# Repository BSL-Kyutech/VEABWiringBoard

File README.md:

# VEABWiringBoard
A board (60mm x 185mm) for wiring Festo's VEAB valves to VEABControlShield

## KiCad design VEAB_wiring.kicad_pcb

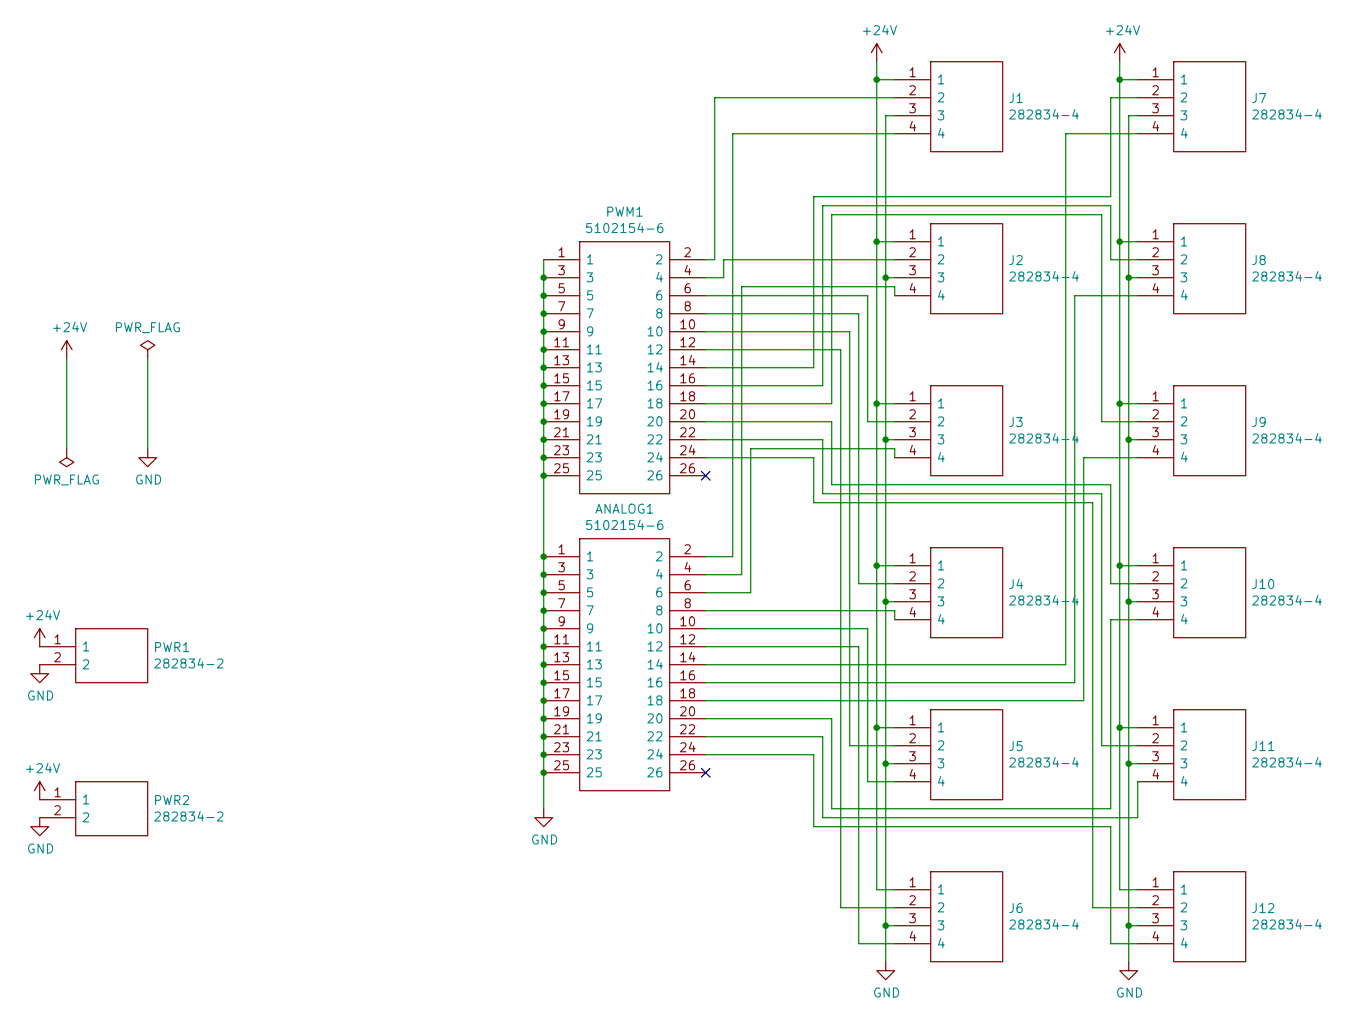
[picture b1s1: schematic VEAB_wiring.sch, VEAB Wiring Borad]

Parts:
ANALOG1: 5102154-6; SHDR26W66P254_2X13_4051X986X927P; Manufacturer_Part_Number 5102154-6
J1, J2, J3, J4, J5, J6, J7, J8, J9, J10, J11, J12: 282834-4; 2828344; Manufacturer_Part_Number 282834-4
PWM1: 5102154-6; SHDR26W66P254_2X13_4051X986X927P; Manufacturer_Part_Number 5102154-6
PWR1, PWR2: 282834-2; 282834-2_1; Manufacturer_Part_Number 282834-2

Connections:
+24V: J1.1, J2.1, J3.1, J4.1, J5.1, J6.1, J7.1, J8.1, J9.1, J10.1, J11.1, J12.1, PWR1.1, PWR2.1
GND: ANALOG1.1, ANALOG1.3, ANALOG1.5, ANALOG1.7, ANALOG1.9, ANALOG1.11, ANALOG1.13, ANALOG1.15, ANALOG1.17, ANALOG1.19, ANALOG1.21, ANALOG1.23, ANALOG1.25, J1.3, J2.3, J3.3, J4.3, J5.3, J6.3, J7.3, J8.3, J9.3, J10.3, J11.3, J12.3, PWM1.1, PWM1.3, PWM1.5, PWM1.7, PWM1.9, PWM1.11, PWM1.13, PWM1.15, PWM1.17, PWM1.19, PWM1.21, PWM1.23, PWM1.25, PWR1.2, PWR2.2
unnamed: ANALOG1.2, J1.4
unnamed: ANALOG1.4, J2.4
unnamed: ANALOG1.6, J3.4
unnamed: ANALOG1.8, J4.4
unnamed: ANALOG1.10, J5.4
unnamed: ANALOG1.12, J6.4
unnamed: ANALOG1.14, J7.4
unnamed: ANALOG1.16, J8.4
unnamed: ANALOG1.18, J9.4
unnamed: ANALOG1.20, J10.4
unnamed: ANALOG1.22, J11.4
unnamed: ANALOG1.24, J12.4
unnamed: J1.2, PWM1.2
unnamed: J2.2, PWM1.4
unnamed: J3.2, PWM1.6
unnamed: J4.2, PWM1.8
unnamed: J5.2, PWM1.10
unnamed: J6.2, PWM1.12
unnamed: J7.2, PWM1.14
unnamed: J8.2, PWM1.16
unnamed: J9.2, PWM1.18
unnamed: J10.2, PWM1.20
unnamed: J11.2, PWM1.22
unnamed: J12.2, PWM1.24

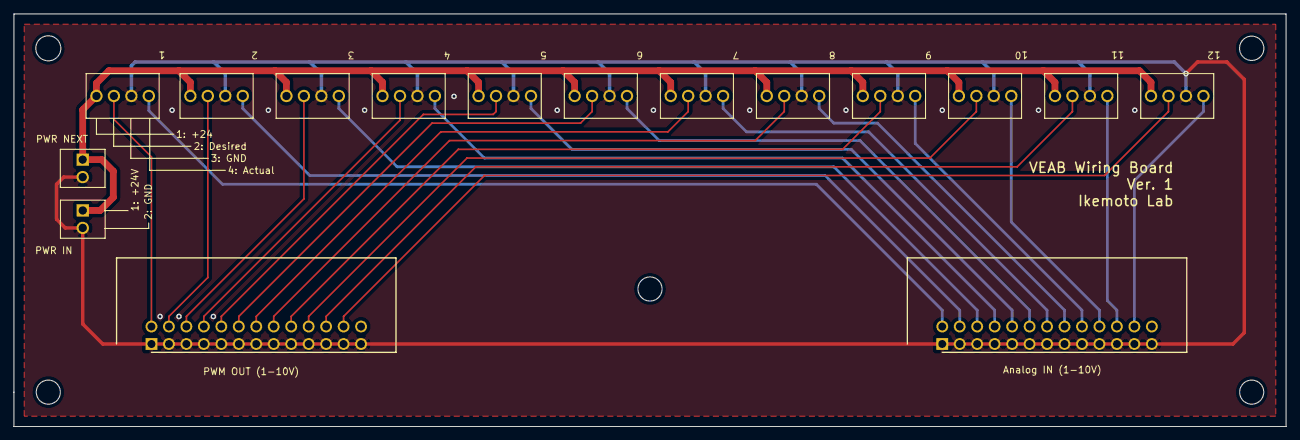
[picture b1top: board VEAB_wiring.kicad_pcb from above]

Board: 2 copper layers, 185.0 x 60.0 mm, 16 parts (0 on the bottom side), 26 nets.

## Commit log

2021-11-17 Add files via upload
    KiCAD files
2021-11-17 temporary files are removed
